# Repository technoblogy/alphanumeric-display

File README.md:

# Eight-Character Alphanumeric Display
An eight-character alphanumeric LED display with an I2C interface, based on four two-character 14-segment alphanumeric display modules and a low-cost HT16K33 display-driver chip.

For more information see: <http://www.technoblogy.com/show?2ULE>.

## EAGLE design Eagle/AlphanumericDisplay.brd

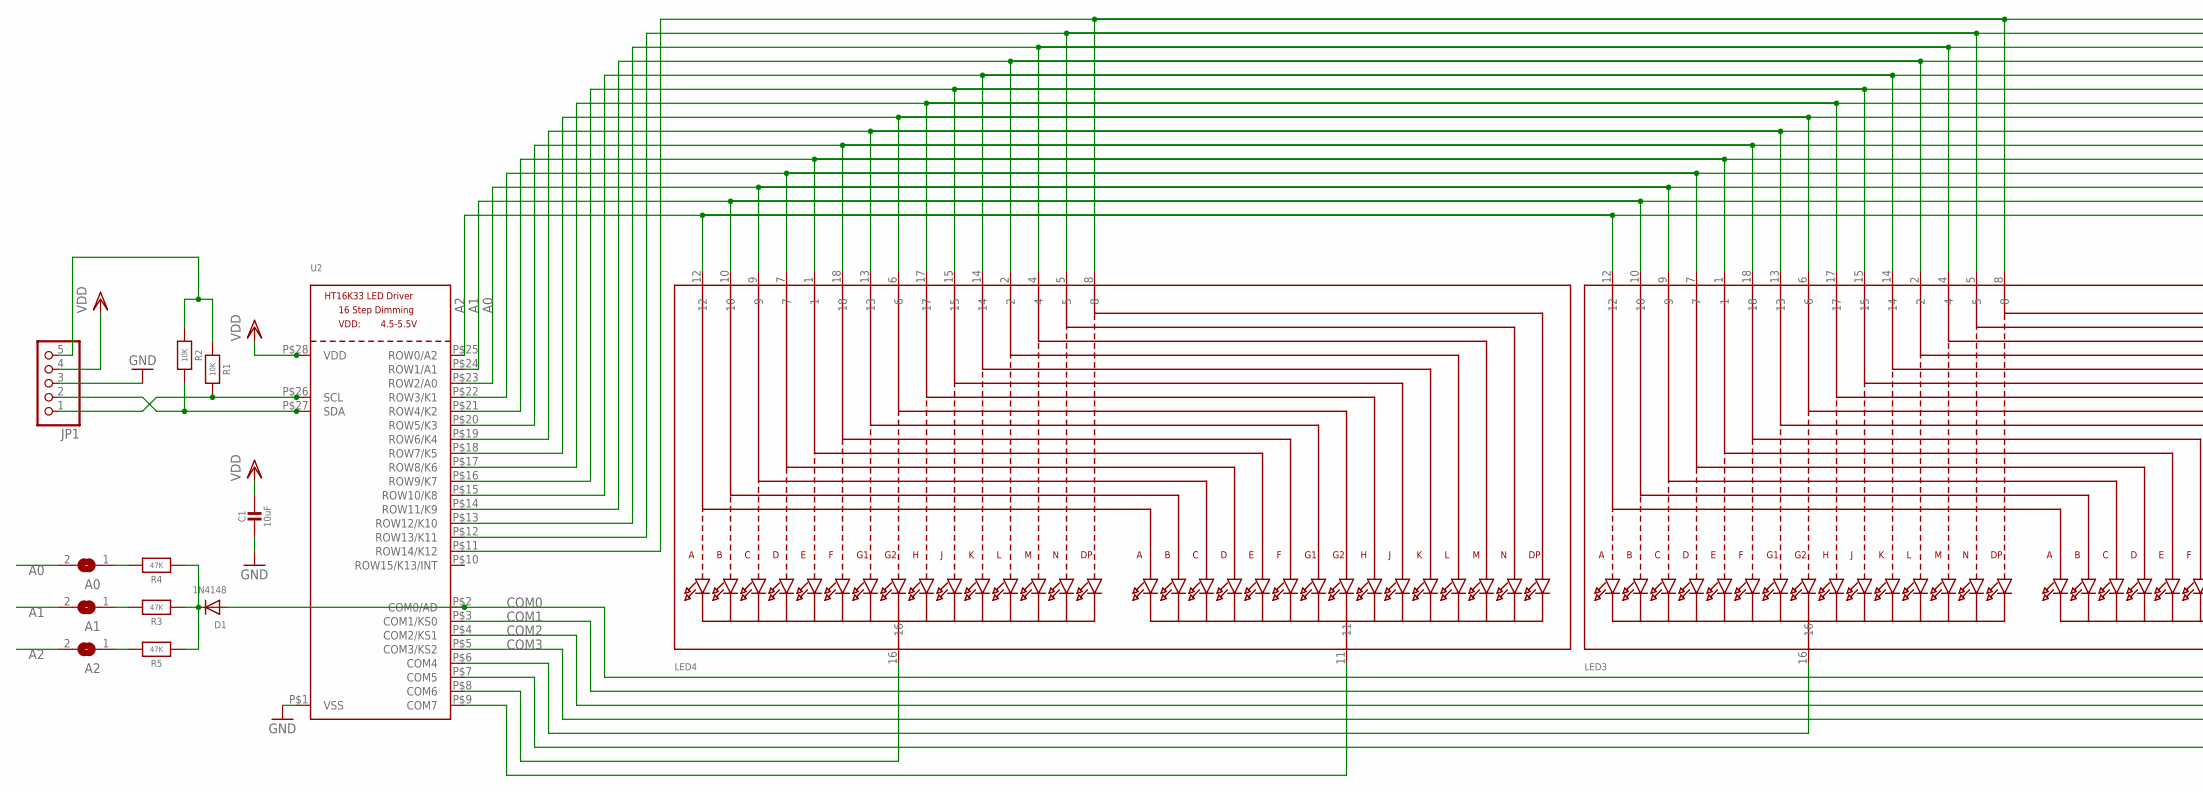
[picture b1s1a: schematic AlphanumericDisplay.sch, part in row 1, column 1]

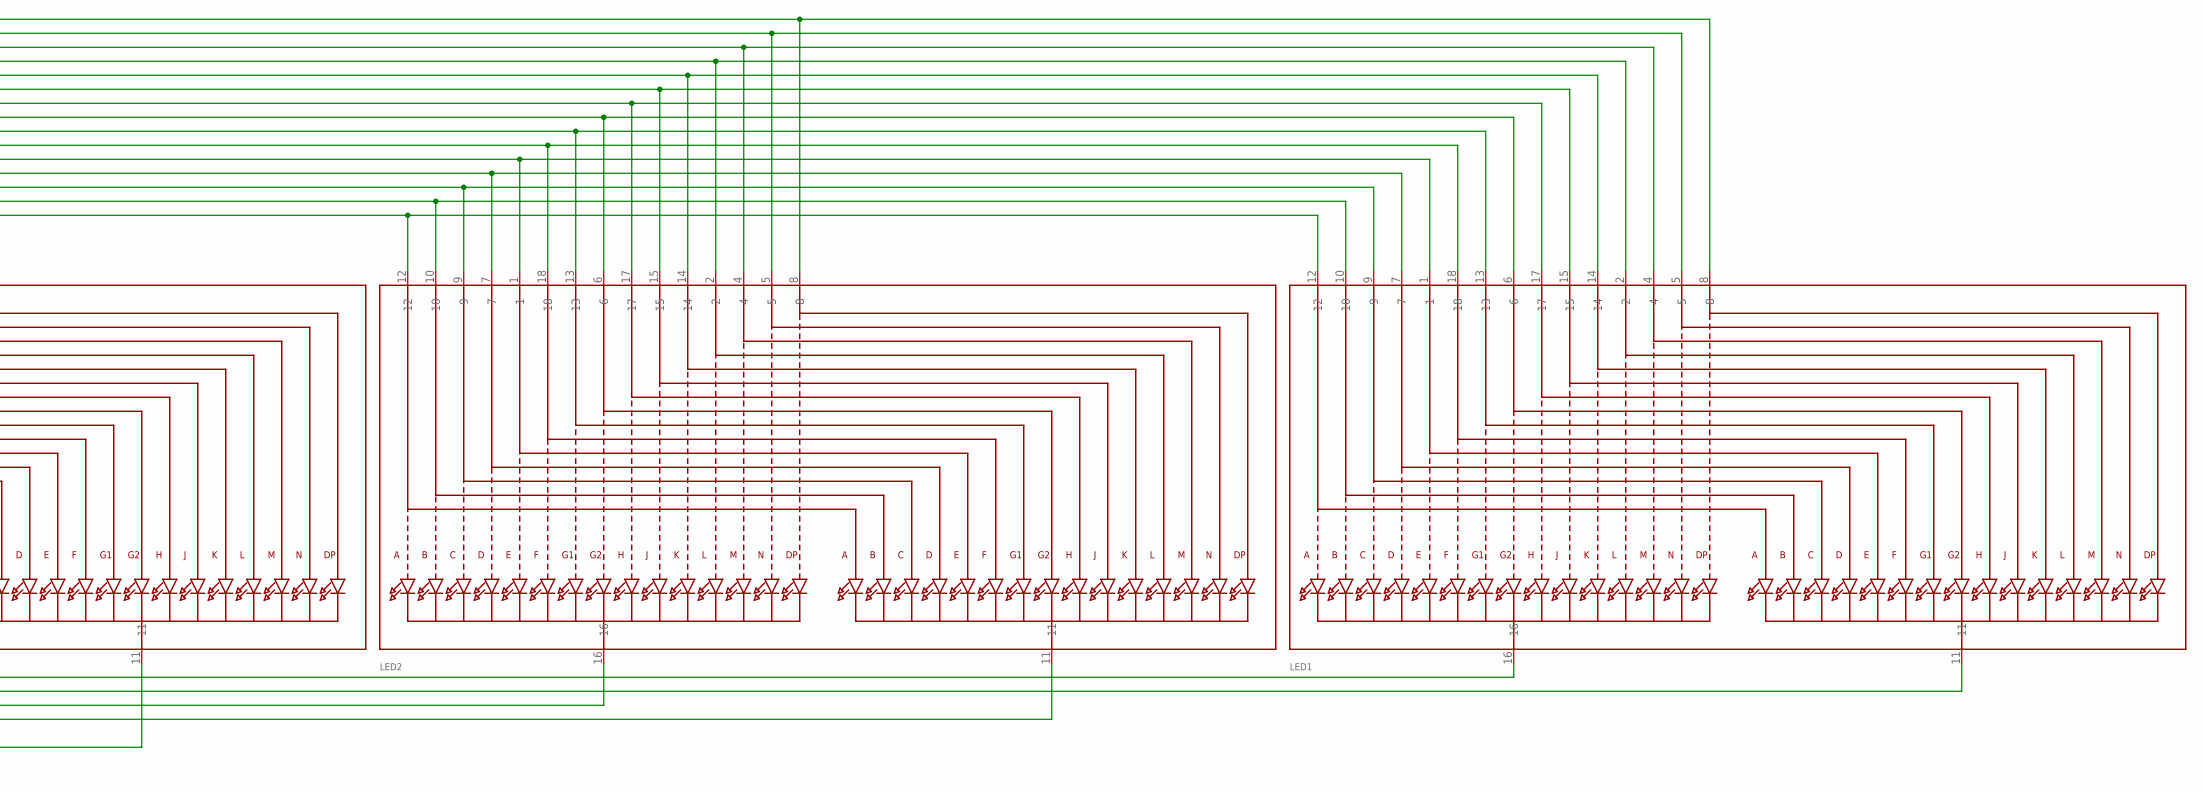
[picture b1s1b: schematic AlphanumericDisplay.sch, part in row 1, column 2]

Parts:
A0, A1, A2: SOLDERJUMPERREFLOW_NOPASTE; SOLDERJUMPER_REFLOW_NOPASTE
C1: 10uF; 0805-NO
D1: 1N4148; SOD-323F
JP1: HEADER-1X570MIL; 1X05_ROUND_70
LED1, LED2, LED3, LED4: DISP_SEGMENT_STARBURST_DUAL_COMMONCATHODE; SEGMENT_STARTBUST_DUAL_KWA-541CBB
R1, R2: 10K; 0805-NO
R3, R4, R5: 47K; 0805-NO
U2: HT16K33_SOP28; SOP28_300MIL

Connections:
A0: A0.2, LED1.9, LED2.9, LED3.9, LED4.9, U2.P$23 (ROW2/A0)
A1: A1.2, LED1.10, LED2.10, LED3.10, LED4.10, U2.P$24 (ROW1/A1)
A2: A2.2, LED1.12, LED2.12, LED3.12, LED4.12, U2.P$25 (ROW0/A2)
COM0: D1.A, LED1.16, U2.P$2 (COM0/AD)
COM1: LED1.11, U2.P$3 (COM1/KS0)
COM2: LED2.16, U2.P$4 (COM2/KS1)
COM3: LED2.11, U2.P$5 (COM3/KS2)
COM4: LED3.16, U2.P$6 (COM4)
COM5: LED3.11, U2.P$7 (COM5)
GND: C1.2, JP1.3, U2.P$1 (VSS)
unnamed: D1.C, R3.1, R4.1, R5.1
unnamed: JP1.5, R1.1, R2.1
unnamed: LED1.17, LED2.17, LED3.17, LED4.17, U2.P$17 (ROW8/K6)
unnamed: LED1.15, LED2.15, LED3.15, LED4.15, U2.P$16 (ROW9/K7)
unnamed: LED1.14, LED2.14, LED3.14, LED4.14, U2.P$15 (ROW10/K8)
unnamed: A2.1, R5.2
unnamed: LED1.2, LED2.2, LED3.2, LED4.2, U2.P$14 (ROW11/K9)
unnamed: LED1.4, LED2.4, LED3.4, LED4.4, U2.P$13 (ROW12/K10)
unnamed: LED1.7, LED2.7, LED3.7, LED4.7, U2.P$22 (ROW3/K1)
unnamed: LED1.1, LED2.1, LED3.1, LED4.1, U2.P$21 (ROW4/K2)
unnamed: LED1.18, LED2.18, LED3.18, LED4.18, U2.P$20 (ROW5/K3)
unnamed: LED1.13, LED2.13, LED3.13, LED4.13, U2.P$19 (ROW6/K4)
unnamed: LED1.5, LED2.5, LED3.5, LED4.5, U2.P$12 (ROW13/K11)
unnamed: LED1.8, LED2.8, LED3.8, LED4.8, U2.P$11 (ROW14/K12)
unnamed: LED1.6, LED2.6, LED3.6, LED4.6, U2.P$18 (ROW7/K5)
unnamed: A1.1, R3.2
unnamed: A0.1, R4.2
unnamed: LED4.16, U2.P$8 (COM6)
unnamed: LED4.11, U2.P$9 (COM7)
SCL: JP1.1, R1.2, U2.P$26 (SCL)
SDA: JP1.2, R2.2, U2.P$27 (SDA)
VDD: C1.1, JP1.4, U2.P$28 (VDD)

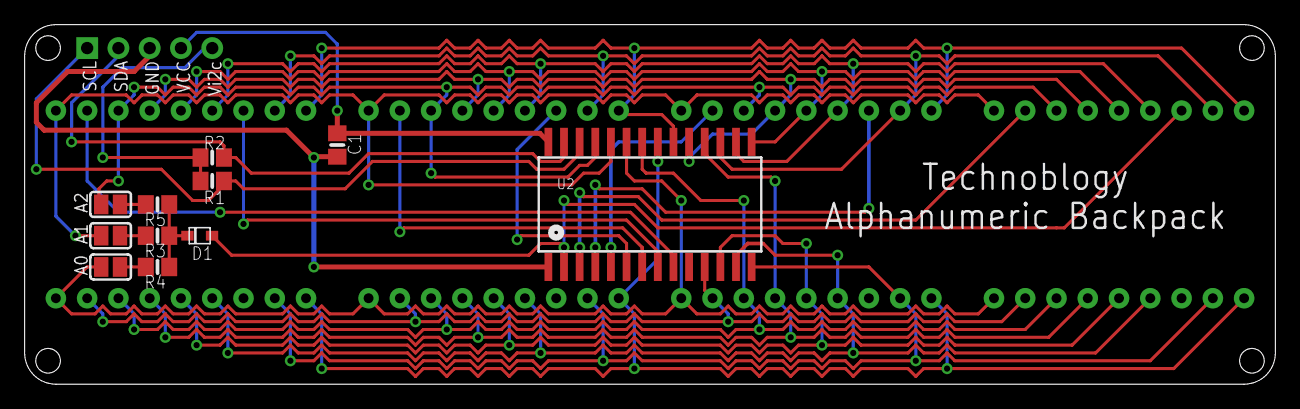
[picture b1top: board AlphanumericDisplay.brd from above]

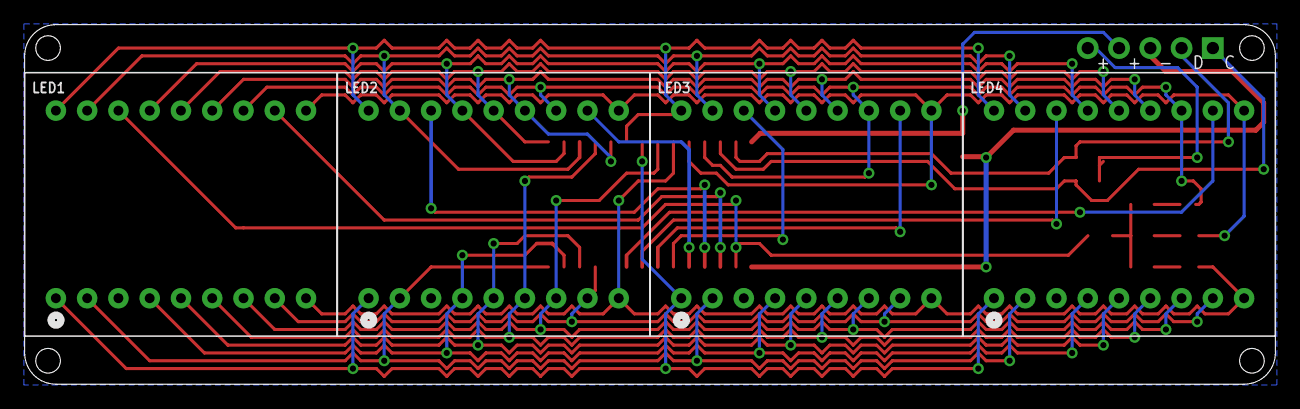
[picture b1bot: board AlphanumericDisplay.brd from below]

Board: 2 copper layers, 101.6 x 29.2 mm, 16 parts (4 on the bottom side), 32 nets.

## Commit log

2019-12-16 Version 1 - 16th December 2019
2020-01-07 Rename folder
2021-12-11 Added Gerber files
